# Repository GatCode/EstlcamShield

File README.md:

# EstlcamShield

## About
The EstlcamShield is a **free** and **open source** PCB design which provides full functionallity of the Estlcam Software. All software-supported pins are provided on the PCB via seperate headers. This shield is specifically designed to work with the [MPCNC](https://www.v1engineering.com/specifications/).

## Component List
- 1x Arduino Mega 2560
- 3x DRV8825 Stepper Driver Board
- 3x 35V 100uF Capacitor (Through Hole)
- 1x KF301-2P Terminal Block (or simmilar)
- 0-9x jumper cap for microstepping
- long female pin headers 2.54mm (I used 8 pin ones)
- regular male pin headers 2.54mm

## Getting Started
You basically have **three** different options:
- Use the included .zip folder, which contains Gerber files, to order your custom PCB from a manufacturer of your choice
- Etch or mill the PCB yourself
- Hit me up on Gitter or via eMail because I ordered a few spare PCBs which I am not using

After you have produced/bought the PCB, solder the necessary components and stack the shield onto your Arduino Mega 2560. Then connect it to your computer and flash the Arduino in the settings of the Estlcam software. You can find good videos about this process on YouTube (the process is simmilar on the Arduino Uno).

Congratulations, you are now running Estlcam in combination with your Arduino Mega! Enjoy 🎉

## License Information

This PCB shield design is based on the [MegaShield_Kit](https://github.com/sparkfun/MegaShield_Kit) from SparkFun, which provided the basic dimensions of the PCB -> Thank you very much!

The hardware is released under [Creative Commons ShareAlike 4.0 International](https://creativecommons.org/licenses/by-sa/4.0/).

## Limitations
This PCB Design is provided as-is!

Please feel free to adapt it to your needs. I would be very grateful to include your inprovements. Thanks for your support!

**WARNING:** Everyone is responsible for what he/she is doing! I am not responsible if you hurt yourself, torch your house or anything that kind trying to build your own CNC! You are doing everything at your own risk!

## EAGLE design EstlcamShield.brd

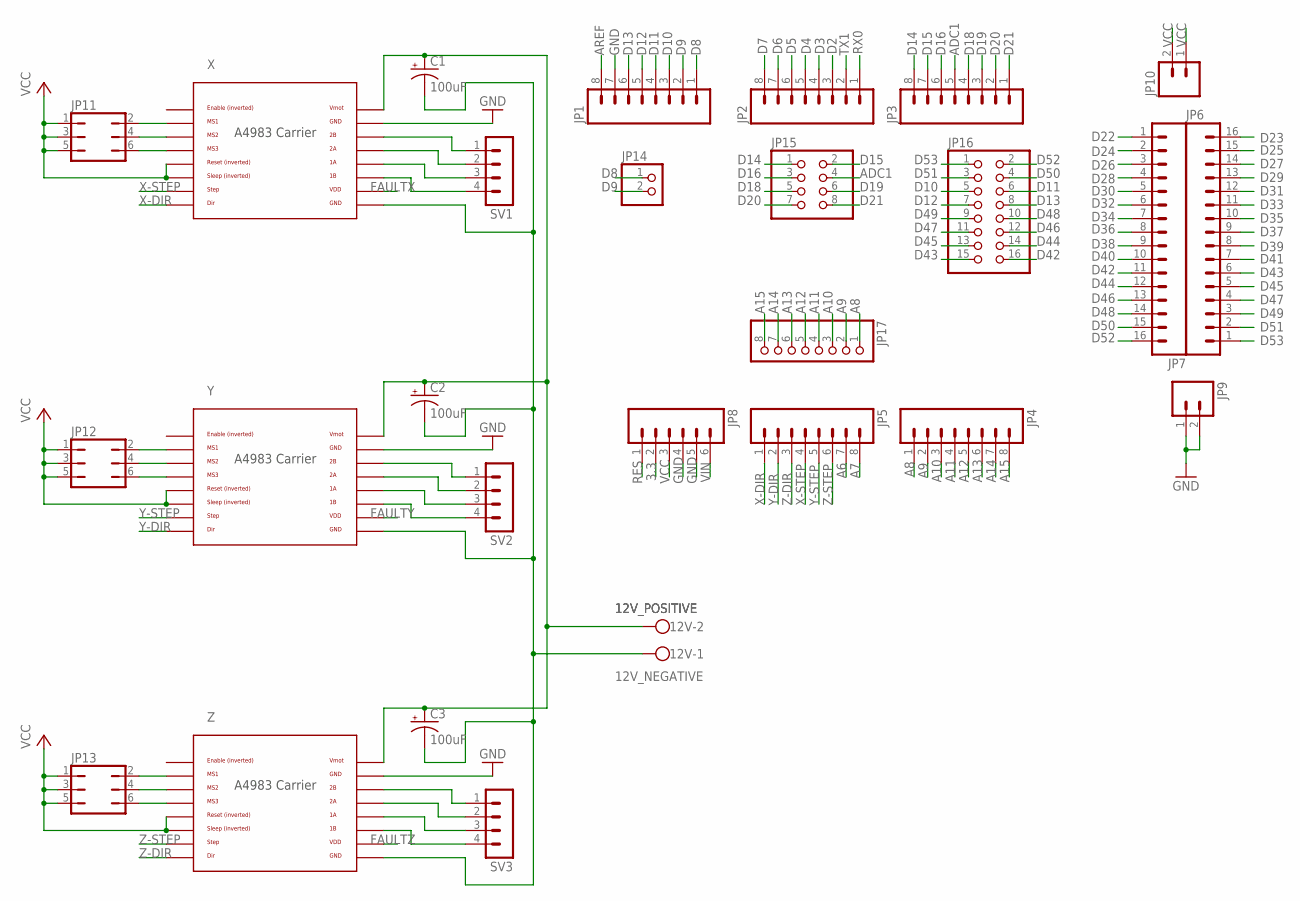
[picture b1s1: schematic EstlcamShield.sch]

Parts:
12V: POSITIVE; W237-102
C1, C2, C3: 100uF; E2,5-5
JP1, JP2, JP3, JP4, JP5: M08LOCK; 1X08_LOCK
JP6, JP7: M16LOCK; 1X16_LOCK
JP8: M06LOCK; 1X06_LOCK
JP9, JP10: M02LOCK; 1X02_LOCK
JP11, JP12, JP13: JP3Q
JP14: PINHD-1X2; 1X02
JP15: PINHD-2X4; 2X04
JP16: PINHD-2X8; 2X08
JP17: PINHD-1X8; 1X08
SV1, SV2, SV3: MA04-1
U2, U3, U4: POLOLU_A4983CARRIER; A4983CARRIER

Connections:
3.3: JP8.2
12V_NEGATIVE: 12V.1, C1.-, C2.-, C3.-, U2.GND@0 (GND), U3.GND@0 (GND), U4.GND@0 (GND)
12V_POSITIVE: 12V.2, C1.+, C2.+, C3.+, U2.VMOT, U3.VMOT, U4.VMOT
A6: JP5.7
A7: JP5.8
A8: JP4.1, JP17.1
A9: JP4.2, JP17.2
A10: JP4.3, JP17.3
A11: JP4.4, JP17.4
A12: JP4.5, JP17.5
A13: JP4.6, JP17.6
A14: JP4.7, JP17.7
A15: JP4.8, JP17.8
ADC1: JP3.5, JP15.4
AREF: JP1.8
D2: JP2.3
D3: JP2.4
D4: JP2.5
D5: JP2.6
D6: JP2.7
D7: JP2.8
D8: JP1.1, JP14.1
D9: JP1.2, JP14.2
D10: JP1.3, JP16.5
D11: JP1.4, JP16.6
D12: JP1.5, JP16.7
D13: JP1.6, JP16.8
D14: JP3.8, JP15.1
D15: JP3.7, JP15.2
D16: JP3.6, JP15.3
D18: JP3.4, JP15.5
D19: JP3.3, JP15.6
D20: JP3.2, JP15.7
D21: JP3.1, JP15.8
D22: JP7.1
D23: JP6.16
D24: JP7.2
D25: JP6.15
D26: JP7.3
D27: JP6.14
D28: JP7.4
D29: JP6.13
D30: JP7.5
D31: JP6.12
D32: JP7.6
D33: JP6.11
D34: JP7.7
D35: JP6.10
D36: JP7.8
D37: JP6.9
D38: JP7.9
D39: JP6.8
D40: JP7.10
D41: JP6.7
D42: JP7.11, JP16.16
D43: JP6.6, JP16.15
D44: JP7.12, JP16.14
D45: JP6.5, JP16.13
D46: JP7.13, JP16.12
D47: JP6.4, JP16.11
D48: JP7.14, JP16.10
D49: JP6.3, JP16.9
D50: JP7.15, JP16.4
D51: JP6.2, JP16.3
D52: JP7.16, JP16.2
D53: JP6.1, JP16.1
FAULTX: U2.VDD
FAULTY: U3.VDD
FAULTZ: U4.VDD
GND: JP1.7, JP8.4, JP8.5, JP9.1, JP9.2, U2.GND, U3.GND, U4.GND
unnamed: JP11.2, U2.MS1
unnamed: JP11.4, U2.MS2
unnamed: JP12.2, U3.MS1
unnamed: JP12.4, U3.MS2
unnamed: JP13.2, U4.MS1
unnamed: JP11.6, U2.MS3
unnamed: JP13.4, U4.MS2
unnamed: SV3.1, U4.2B
unnamed: SV3.2, U4.2A
unnamed: SV3.3, U4.1A
unnamed: SV3.4, U4.1B
unnamed: SV2.1, U3.2B
unnamed: SV2.2, U3.2A
unnamed: SV2.3, U3.1A
unnamed: SV2.4, U3.1B
unnamed: SV1.1, U2.2B
unnamed: JP13.6, U4.MS3
unnamed: SV1.2, U2.2A
unnamed: JP12.6, U3.MS3
unnamed: SV1.3, U2.1A
unnamed: SV1.4, U2.1B
RES: JP8.1
RX0: JP2.1
TX1: JP2.2
VCC: JP8.3, JP10.1, JP10.2, JP11.1, JP11.3, JP11.5, JP12.1, JP12.3, JP12.5, JP13.1, JP13.3, JP13.5, U2.RST, U2.SLP (SLEEP), U3.RST, U3.SLP (SLEEP), U4.RST, U4.SLP (SLEEP)
VIN: JP8.6
X-DIR: JP5.1, U2.DIR
X-STEP: JP5.4, U2.STEP
Y-DIR: JP5.2, U3.DIR
Y-STEP: JP5.5, U3.STEP
Z-DIR: JP5.3, U4.DIR
Z-STEP: JP5.6, U4.STEP

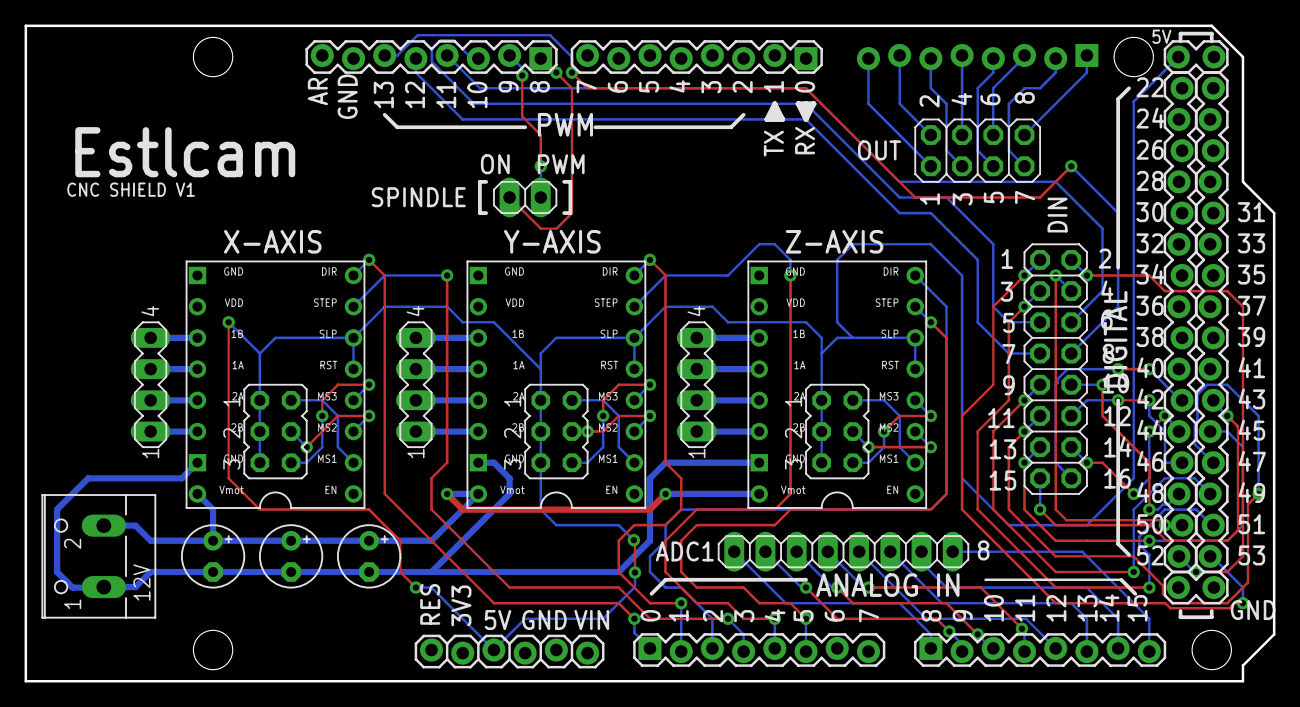
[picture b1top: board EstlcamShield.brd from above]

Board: 2 copper layers, 101.6 x 53.3 mm, 27 parts (1 on the bottom side), 65 nets.

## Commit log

2019-01-28 Add Files
2019-03-20 Add images
2019-03-20 Add Main Image
2019-03-20 Update Readme Image

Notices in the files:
README.md:
License: CC BY-SA 4.0
